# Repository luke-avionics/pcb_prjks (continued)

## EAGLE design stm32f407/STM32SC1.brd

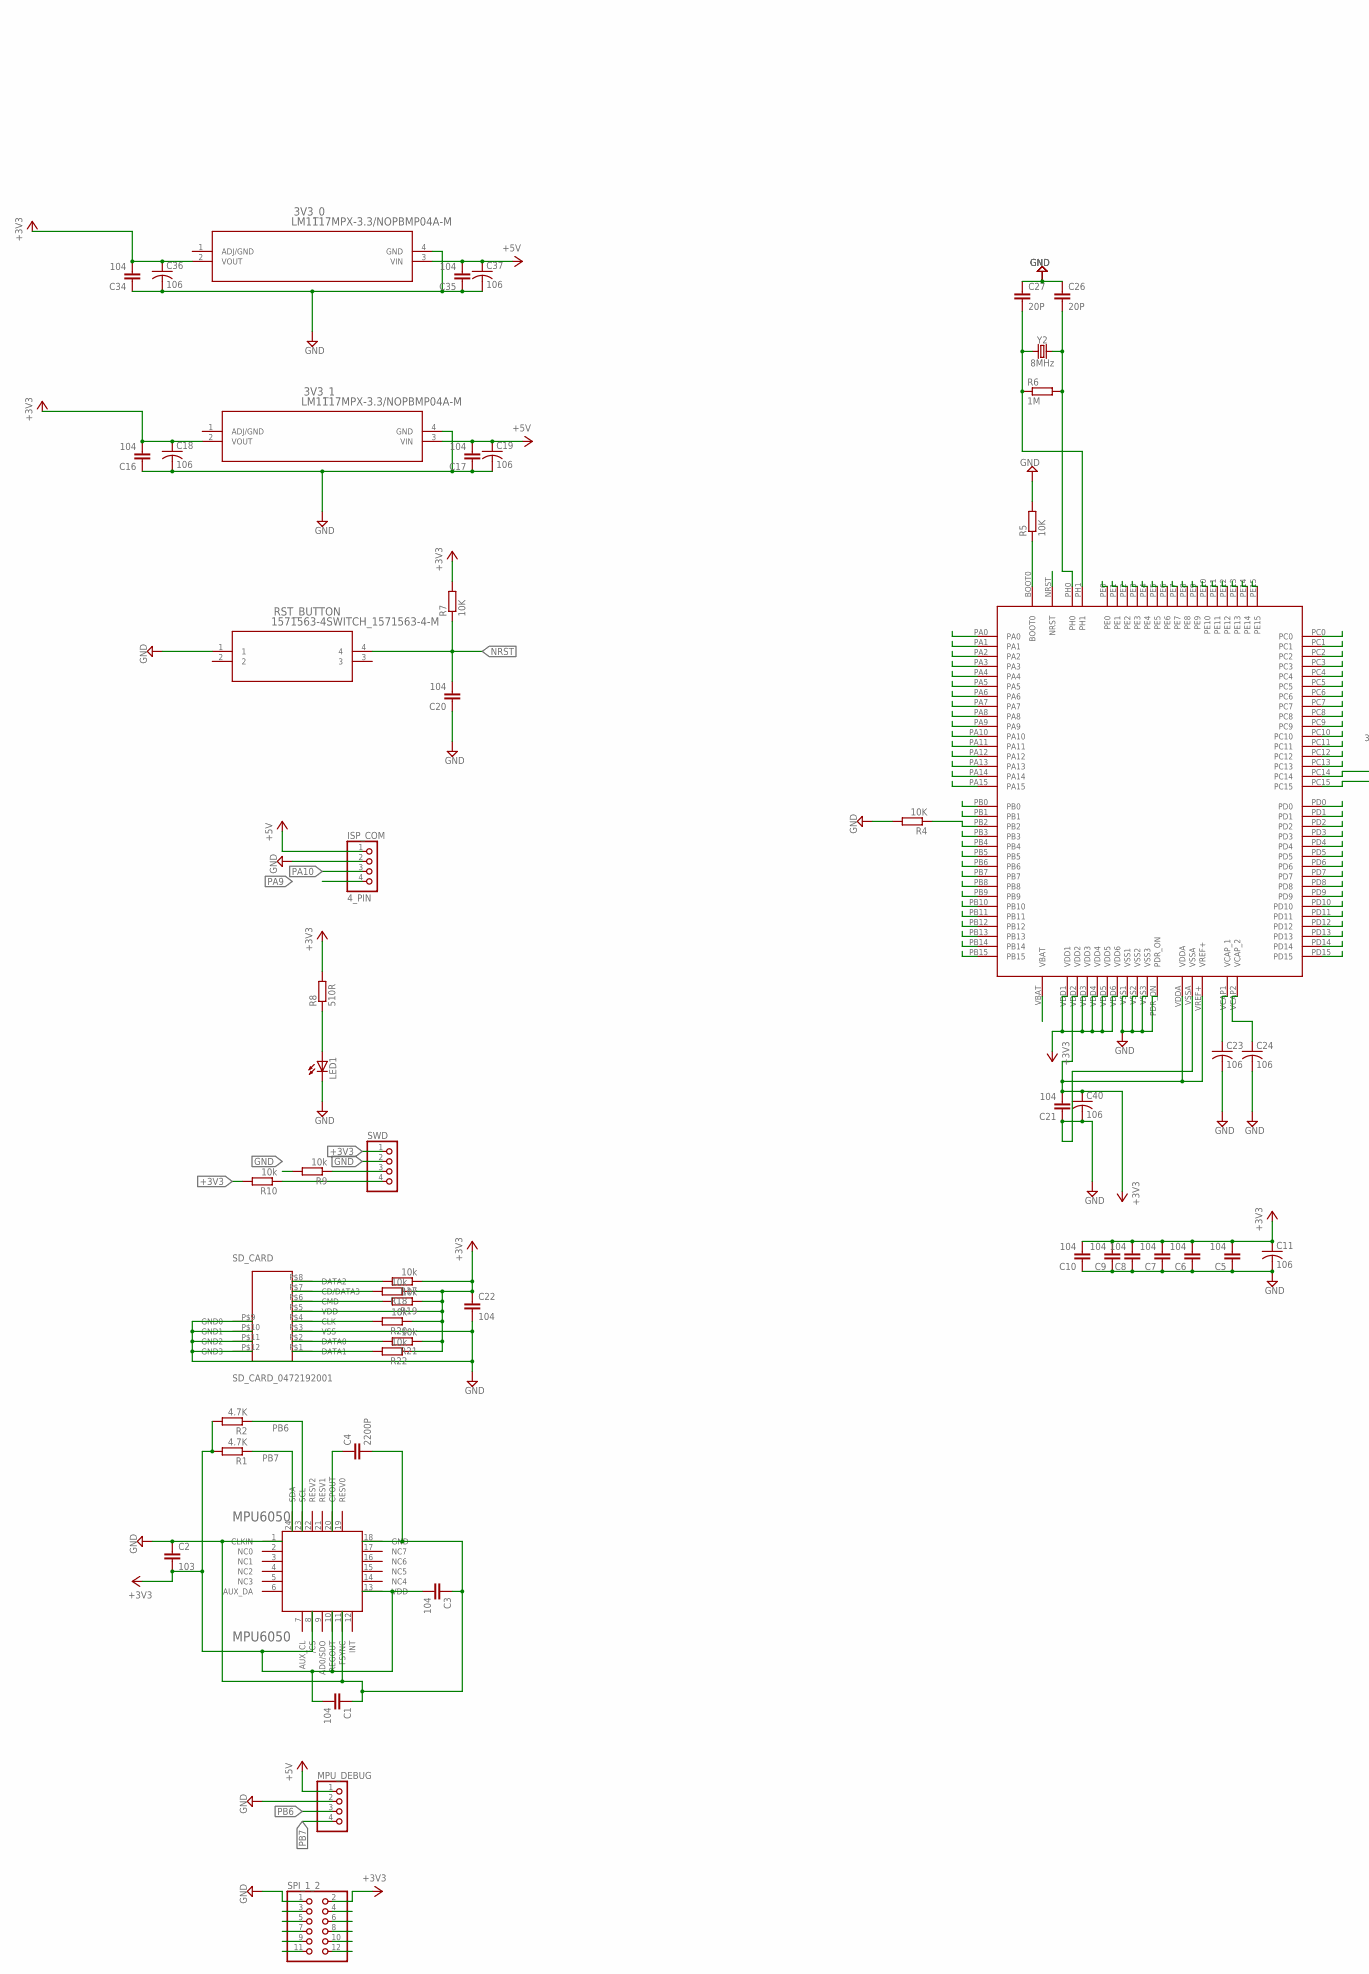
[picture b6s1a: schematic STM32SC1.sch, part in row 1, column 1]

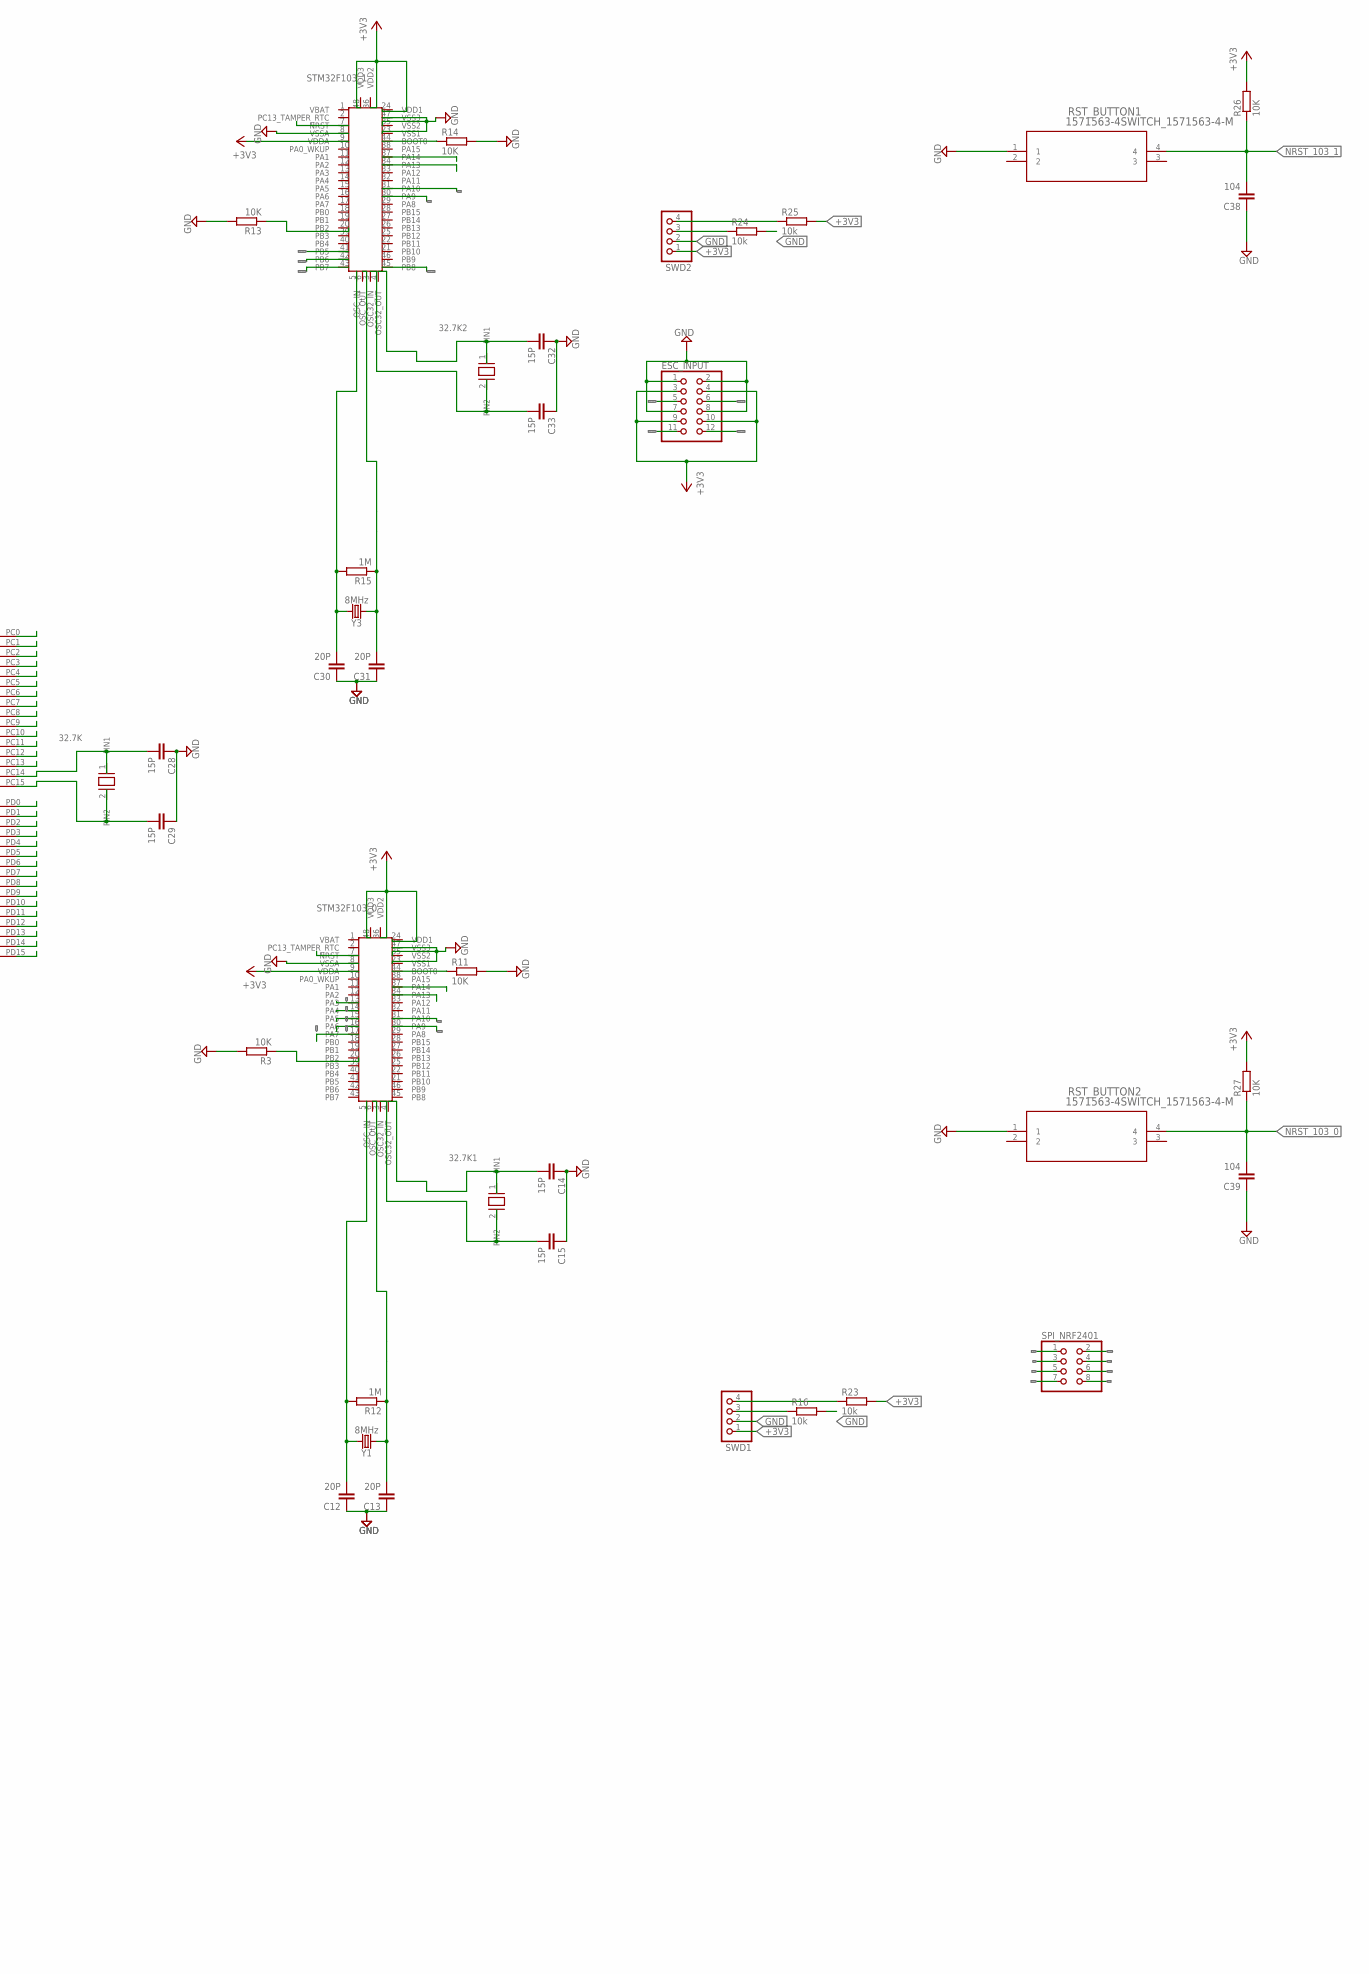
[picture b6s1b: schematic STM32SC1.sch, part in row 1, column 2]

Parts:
3V3_0, 3V3_1: LM1117MPX-3.3/NOPBMP04A-M; MP04A-M
32.7K, 32.7K1, 32.7K2: CM315D; CM315D_32.7K
C1, C3, C5, C6, C7, C8, C9, C10, C16, C17, C20, C21, C22, C34, C35, C38, C39: 104; C0603
C2: 103; C0603
C4: 2200P; C0603
C11, C18, C19, C23, C24, C36, C37, C40: 106; C0805
C12, C13, C26, C27, C30, C31: 20P; C0603
C14, C15, C28, C29, C32, C33: 15P; C0603
ESC_INPUT: PINHD-2X6/90; 2X06/90
ISP_COM: 4_PIN; 1X04
LED1: LEDCHIPLED_0805; CHIPLED_0805
MPU6050: MPU6050
MPU_DEBUG: PINHD-1X4; 1X04
R1, R2: 4.7K; R0603
R3, R4, R5, R7, R11, R13, R14, R26, R27: 10K; R0603
R6, R12, R15: 1M; R0603
R8: 510R; R0603
R9, R10, R16, R17, R18, R19, R20, R21, R22, R23, R24, R25: 10k; R0603
RST_BUTTON, RST_BUTTON1, RST_BUTTON2: 1571563-4SWITCH_1571563-4-M; SWITCH_1571563-4-M
SD_CARD: SD_CARD_0472192001; 0472192001
SPI_1_2: PINHD-2X6/90; 2X06/90
SPI_NRF2401: PINHD-2X4; 2X04
STM32F103_0, STM32F103_1: STM32F103C8T6; STM32103C8T6_LQFP48
SWD, SWD1, SWD2: PINHD-1X4; 1X04
U$1: STM32F4V_100PIN_GENERIC; LQFP100
Y1, Y2, Y3: 8MHz; HC49UP

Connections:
+3V3: 3V3_0.2 (VOUT), 3V3_1.2 (VOUT), C1.2, C2.2, C3.2, C5.2, C6.2, C7.2, C8.2, C9.2, C10.2, C11.1, C16.2, C18.1, C21.2, C22.1, C34.2, C36.1, C40.1, ESC_INPUT.3, ESC_INPUT.4, ESC_INPUT.9, ESC_INPUT.10, MPU6050.8 (/CS), MPU6050.10 (REGOUT), MPU6050.13 (VDD), R1.2, R2.2, R7.2, R8.2, R10.2, R17.1, R18.1, R19.1, R20.1, R21.1, R22.1, R23.2, R25.2, R26.2, R27.2, SD_CARD.P$5 (VDD), SPI_1_2.2, SPI_NRF2401.2, STM32F103_0.9 (VDDA), STM32F103_0.24 (VDD1), STM32F103_0.36 (VDD2), STM32F103_0.48 (VDD3), STM32F103_1.9 (VDDA), STM32F103_1.24 (VDD1), STM32F103_1.36 (VDD2), STM32F103_1.48 (VDD3), SWD.1, SWD1.1, SWD2.1, U$1.VDD1, U$1.VDD2, U$1.VDD3, U$1.VDD4, U$1.VDD5, U$1.VDD6, U$1.VDDA, U$1.VREF+
+5V: 3V3_0.3 (VIN), 3V3_1.3 (VIN), C17.2, C19.1, C35.2, C37.1, ISP_COM.1, MPU_DEBUG.1
BOOT0: R5.1, U$1.BOOT0
CE: SPI_NRF2401.3, STM32F103_0.13 (PA3)
CSN: SPI_NRF2401.4, STM32F103_0.14 (PA4)
GND: 3V3_0.4 (GND), 3V3_1.4 (GND), C1.1, C2.1, C3.1, C4.2, C5.1, C6.1, C7.1, C8.1, C9.1, C10.1, C11.2, C12.1, C13.1, C14.1, C15.1, C16.1, C17.1, C18.2, C19.2, C20.1, C21.1, C22.2, C23.2, C24.2, C26.1, C27.1, C28.1, C29.1, C30.1, C31.1, C32.1, C33.1, C34.1, C35.1, C36.2, C37.2, C38.1, C39.1, C40.2, ESC_INPUT.1, ESC_INPUT.2, ESC_INPUT.7, ESC_INPUT.8, ISP_COM.2, LED1.C, MPU6050.1 (CLKIN), MPU6050.11 (FSYNC), MPU6050.18 (GND), MPU_DEBUG.2, R3.2, R4.2, R5.2, R9.2, R11.2, R13.2, R14.2, R16.2, R24.2, RST_BUTTON.1, RST_BUTTON1.1, RST_BUTTON2.1, SD_CARD.P$3 (VSS), SD_CARD.P$9 (GND0), SD_CARD.P$10 (GND1), SD_CARD.P$11 (GND2), SD_CARD.P$12 (GND3), SPI_1_2.1, SPI_NRF2401.1, STM32F103_0.8 (VSSA), STM32F103_0.23 (VSS1), STM32F103_0.35 (VSS2), STM32F103_0.47 (VSS3), STM32F103_1.8 (VSSA), STM32F103_1.23 (VSS1), STM32F103_1.35 (VSS2), STM32F103_1.47 (VSS3), SWD.2, SWD1.2, SWD2.2, U$1.PDR_ON, U$1.VSS1, U$1.VSS2, U$1.VSS3, U$1.VSSA
IRQ: SPI_NRF2401.8
MISO: SPI_NRF2401.7, STM32F103_0.16 (PA6)
MOSI: SPI_NRF2401.6, STM32F103_0.17 (PA7)
MOTOR1: ESC_INPUT.5, STM32F103_1.41 (PB5)
MOTOR2: ESC_INPUT.11, STM32F103_1.42 (PB6)
MOTOR3: ESC_INPUT.6, STM32F103_1.43 (PB7)
MOTOR4: ESC_INPUT.12, STM32F103_1.45 (PB8)
unnamed: LED1.A, R8.1
unnamed: R14.1, STM32F103_1.44 (BOOT0)
unnamed: C4.1, MPU6050.20 (CPOUT)
unnamed: R11.1, STM32F103_0.44 (BOOT0)
unnamed: R3.1, STM32F103_0.20 (PB2)
unnamed: R13.1, STM32F103_1.20 (PB2)
NRST: C20.2, R7.1, RST_BUTTON.4, U$1.NRST
NRST_103_0: C39.2, R27.1, RST_BUTTON2.4, STM32F103_0.7 (NRST)
NRST_103_1: C38.2, R26.1, RST_BUTTON1.4, STM32F103_1.7 (NRST)
OSC32_IN_1: 32.7K2.2 (PIN2), C33.2, STM32F103_1.3 (OSC32_IN)
OSC32_IN_103: 32.7K1.2 (PIN2), C15.2, STM32F103_0.3 (OSC32_IN)
OSC32_OUT_1: 32.7K2.1 (PIN1), C32.2, STM32F103_1.4 (OSC32_OUT)
OSC32_OUT_103: 32.7K1.1 (PIN1), C14.2, STM32F103_0.4 (OSC32_OUT)
OSC_IN_1: C30.2, R15.2, STM32F103_1.5 (OSC_IN), Y3.2
OSC_IN_103: C12.2, R12.2, STM32F103_0.5 (OSC_IN), Y1.2
OSC_OUT_1: C31.2, R15.1, STM32F103_1.6 (OSC_OUT), Y3.1
OSC_OUT_103: C13.2, R12.1, STM32F103_0.6 (OSC_OUT), Y1.1
PA0: U$1.PA0
PA1: U$1.PA1
PA2: STM32F103_1.31 (PA10), U$1.PA2
PA3: STM32F103_1.30 (PA9), U$1.PA3
PA4: U$1.PA4
PA5: SPI_1_2.7, U$1.PA5
PA6: SPI_1_2.9, U$1.PA6
PA7: SPI_1_2.11, U$1.PA7
PA8: U$1.PA8
PA9: ISP_COM.4, STM32F103_0.31 (PA10), U$1.PA9
PA10: ISP_COM.3, STM32F103_0.30 (PA9), U$1.PA10
PA11: U$1.PA11
PA12: U$1.PA12
PA13: R10.1, SWD.4, U$1.PA13
PA14: R9.1, SWD.3, U$1.PA14
PA15: U$1.PA15
PB0: U$1.PB0
PB1: U$1.PB1
PB2: R4.1, U$1.PB2
PB3: U$1.PB3
PB4: U$1.PB4
PB5: U$1.PB5
PB6: MPU6050.23 (SCL), MPU_DEBUG.3, R2.1, U$1.PB6
PB7: MPU6050.24 (SDA), MPU_DEBUG.4, R1.1, U$1.PB7
PB8: U$1.PB8
PB9: U$1.PB9
PB10: SPI_1_2.8, U$1.PB10
PB11: U$1.PB11
PB12: U$1.PB12
PB13: U$1.PB13
PB14: U$1.PB14
PB15: U$1.PB15
PC0: U$1.PC0
PC1: U$1.PC1
PC2: SPI_1_2.10, U$1.PC2
PC3: SPI_1_2.12, U$1.PC3
PC4: SPI_1_2.3, U$1.PC4
PC5: SPI_1_2.5, U$1.PC5
PC6: U$1.PC6
PC7: U$1.PC7
PC8: R21.2, SD_CARD.P$2 (DATA0), U$1.PC8
PC9: R22.2, SD_CARD.P$1 (DATA1), U$1.PC9
PC10: R17.2, SD_CARD.P$8 (DATA2), U$1.PC10
PC11: R18.2, SD_CARD.P$7 (CD/DATA3), U$1.PC11
PC12: R20.2, SD_CARD.P$4 (CLK), U$1.PC12
PC13: U$1.PC13
PC14: 32.7K.1 (PIN1), C28.2, U$1.PC14
PC15: 32.7K.2 (PIN2), C29.2, U$1.PC15
PD0: U$1.PD0
PD1: U$1.PD1
PD2: R19.2, SD_CARD.P$6 (CMD), U$1.PD2
PD3: U$1.PD3
PD4: U$1.PD4
PD5: U$1.PD5
PD6: U$1.PD6
PD7: U$1.PD7
PD8: U$1.PD8
PD9: U$1.PD9
PD10: U$1.PD10
PD11: U$1.PD11
PD12: U$1.PD12
PD13: U$1.PD13
PD14: U$1.PD14
PD15: U$1.PD15
PE0: U$1.PE0
PE1: U$1.PE1
PE2: U$1.PE2
PE3: U$1.PE3
PE4: U$1.PE4
PE5: U$1.PE5
PE6: U$1.PE6
PE7: SPI_1_2.4, U$1.PE7
PE8: SPI_1_2.6, U$1.PE8
PE9: U$1.PE9
PE10: U$1.PE10
PE11: U$1.PE11
PE12: U$1.PE12
PE13: U$1.PE13
PE14: U$1.PE14
PE15: U$1.PE15
PH0: C26.2, R6.2, U$1.PH0, Y2.2
PH1: C27.2, R6.1, U$1.PH1, Y2.1
SCK: SPI_NRF2401.5, STM32F103_0.15 (PA5)
SWCLK_103_0: R16.1, STM32F103_0.37 (PA14), SWD1.3
SWCLK_103_1: R24.1, STM32F103_1.37 (PA14), SWD2.3
SWDIO_103_0: R23.1, STM32F103_0.34 (PA13), SWD1.4
SWDIO_103_1: R25.1, STM32F103_1.34 (PA13), SWD2.4
VBAT: U$1.VBAT
VCAP1: C23.1, U$1.VCAP1 (VCAP_1)
VCAP2: C24.1, U$1.VCAP2 (VCAP_2)

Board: 2 copper layers, 91 parts (0 on the bottom side), 65 nets, no tracks yet.

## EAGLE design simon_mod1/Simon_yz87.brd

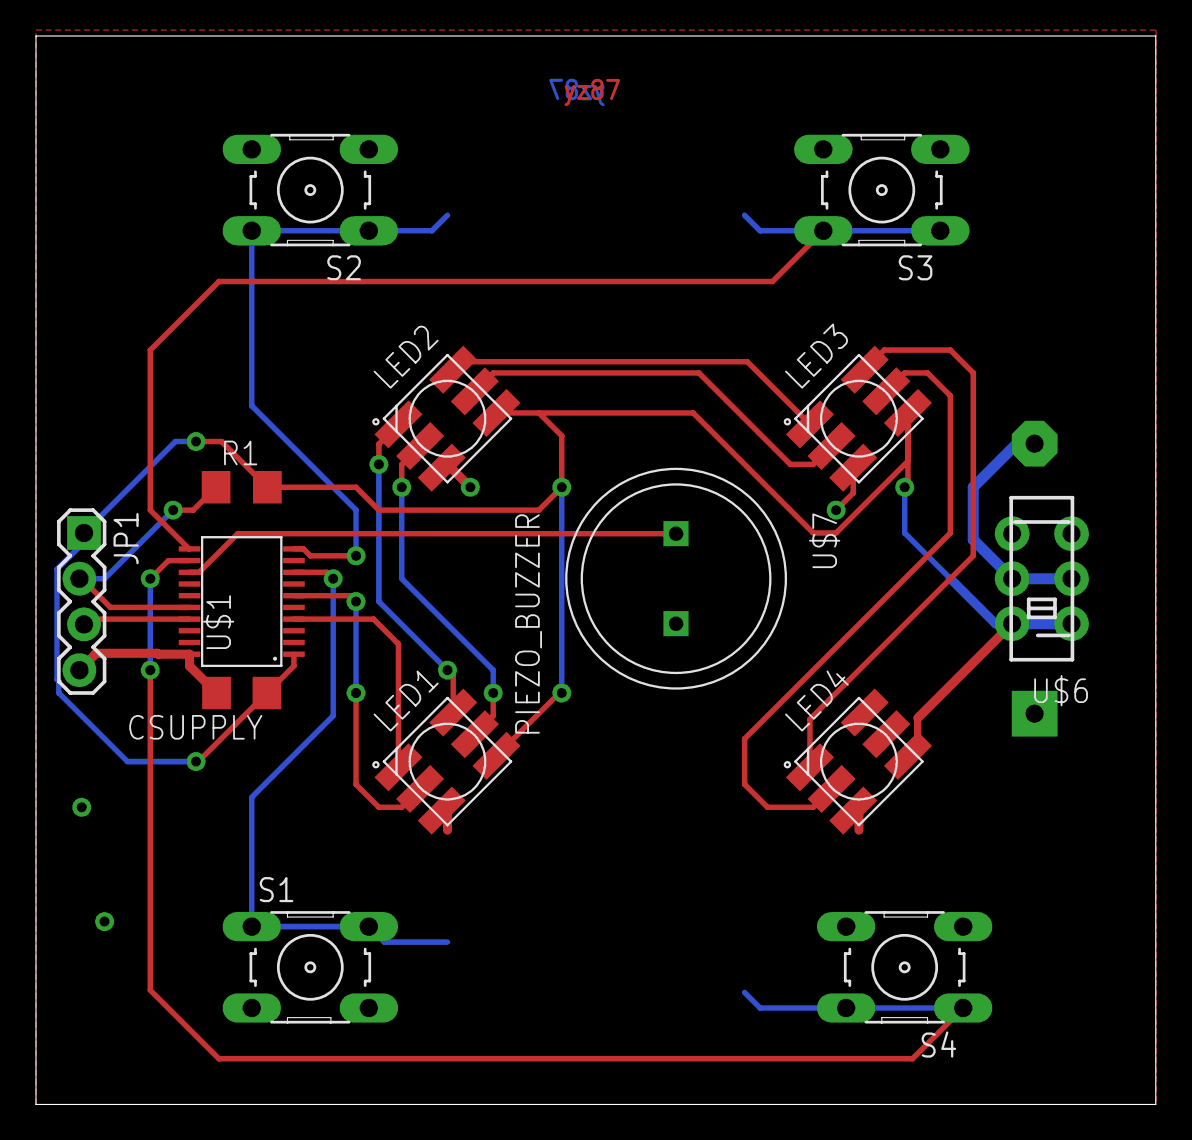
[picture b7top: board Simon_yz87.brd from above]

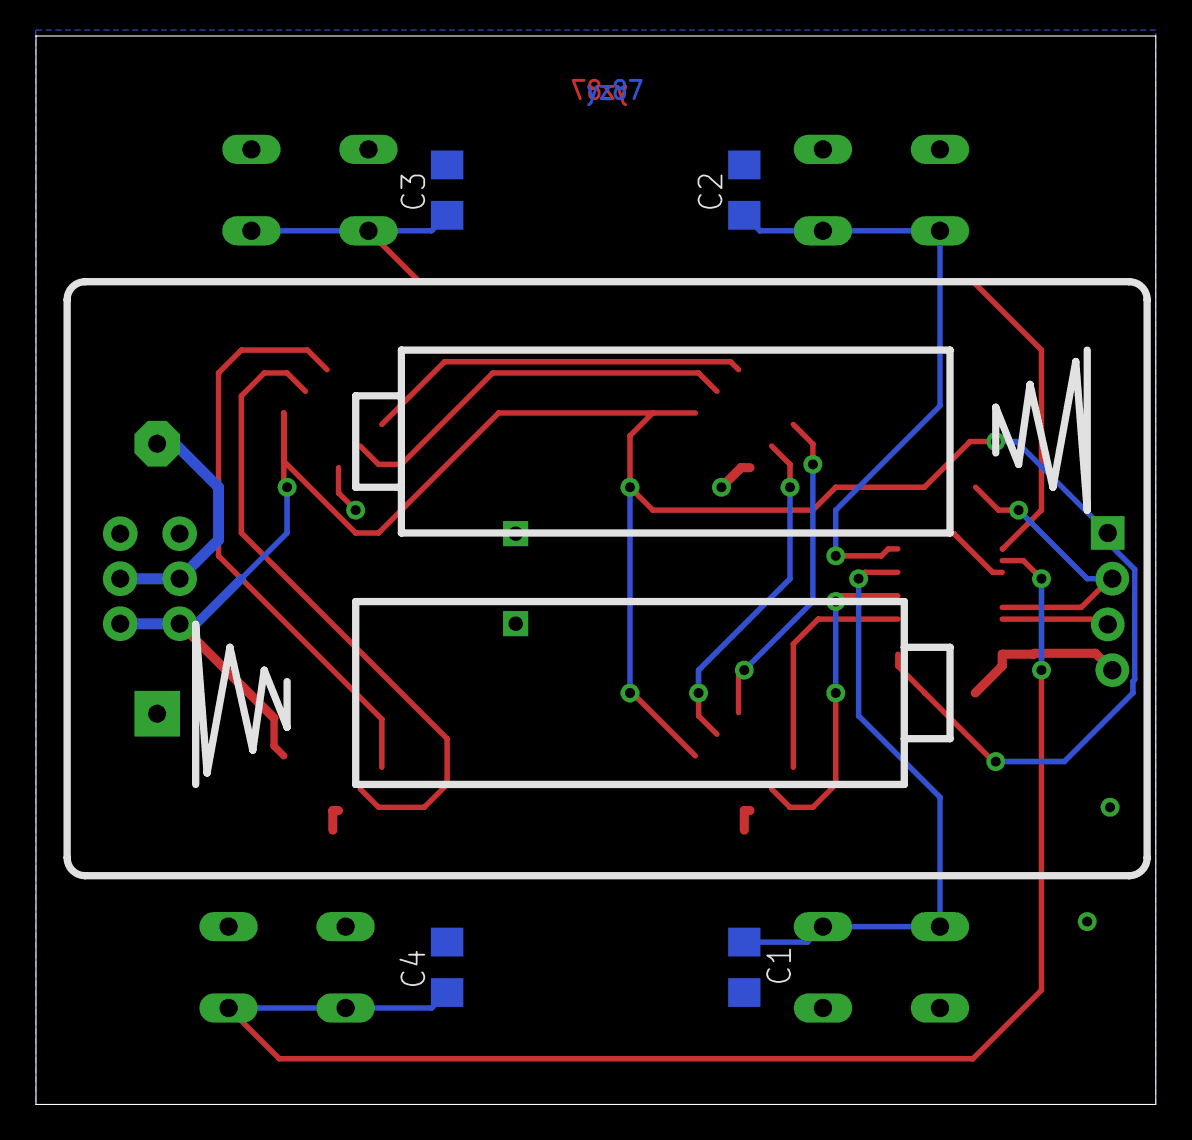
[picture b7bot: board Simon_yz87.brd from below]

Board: 2 copper layers, 62.2 x 59.4 mm, 19 parts (5 on the bottom side), 18 nets.

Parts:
BAT1: BATTERY_PACK_2AA
C1, C2, C3, C4: C1206
CSUPPLY: C1206
JP1: 1X04_LOCK
LED1, LED2, LED3, LED4: APA102; 5050
R1: R1206
S1, S2, S3, S4: B3F-10XX
U$1: MSP430G2XX3TSSOP; PW20
U$6: SWITCH_DPDT; JS_DPDT_TH
U$7: PIEZO_BUZZER

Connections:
BAT_VCC: BAT1.3V, U$6.2, U$6.5
GND: BAT1.GND, C1.2, C2.2, C3.2, C4.2, CSUPPLY.2, JP1.4, LED1.3, LED2.3, LED3.3, LED4.3, S1.3, S1.4, S2.3, S2.4, S3.3, S3.4, S4.3, S4.4, U$1.20, U$7.P$2
unnamed: LED1.6, LED2.1
unnamed: LED1.5, LED2.2
unnamed: LED2.6, LED3.1
unnamed: LED2.5, LED3.2
unnamed: LED3.6, LED4.1
unnamed: LED3.5, LED4.2
unnamed: LED1.1, U$1.4
unnamed: LED1.2, U$1.6
unnamed: U$1.13, U$7.P$1
unnamed: C1.1, S1.1, S1.2, U$1.8
unnamed: C2.1, S2.1, S2.2, U$1.10
unnamed: C3.1, S3.1, S3.2, U$1.11
unnamed: C4.1, S4.1, S4.2, U$1.12
RST: JP1.2, R1.1, U$1.16
TEST: JP1.3, U$1.17
VCC: CSUPPLY.1, JP1.1, LED1.4, LED2.4, LED3.4, LED4.4, R1.2, U$1.1, U$6.1, U$6.4

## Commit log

2018-09-21 audio board 01
2018-10-01 finished audio board 1
